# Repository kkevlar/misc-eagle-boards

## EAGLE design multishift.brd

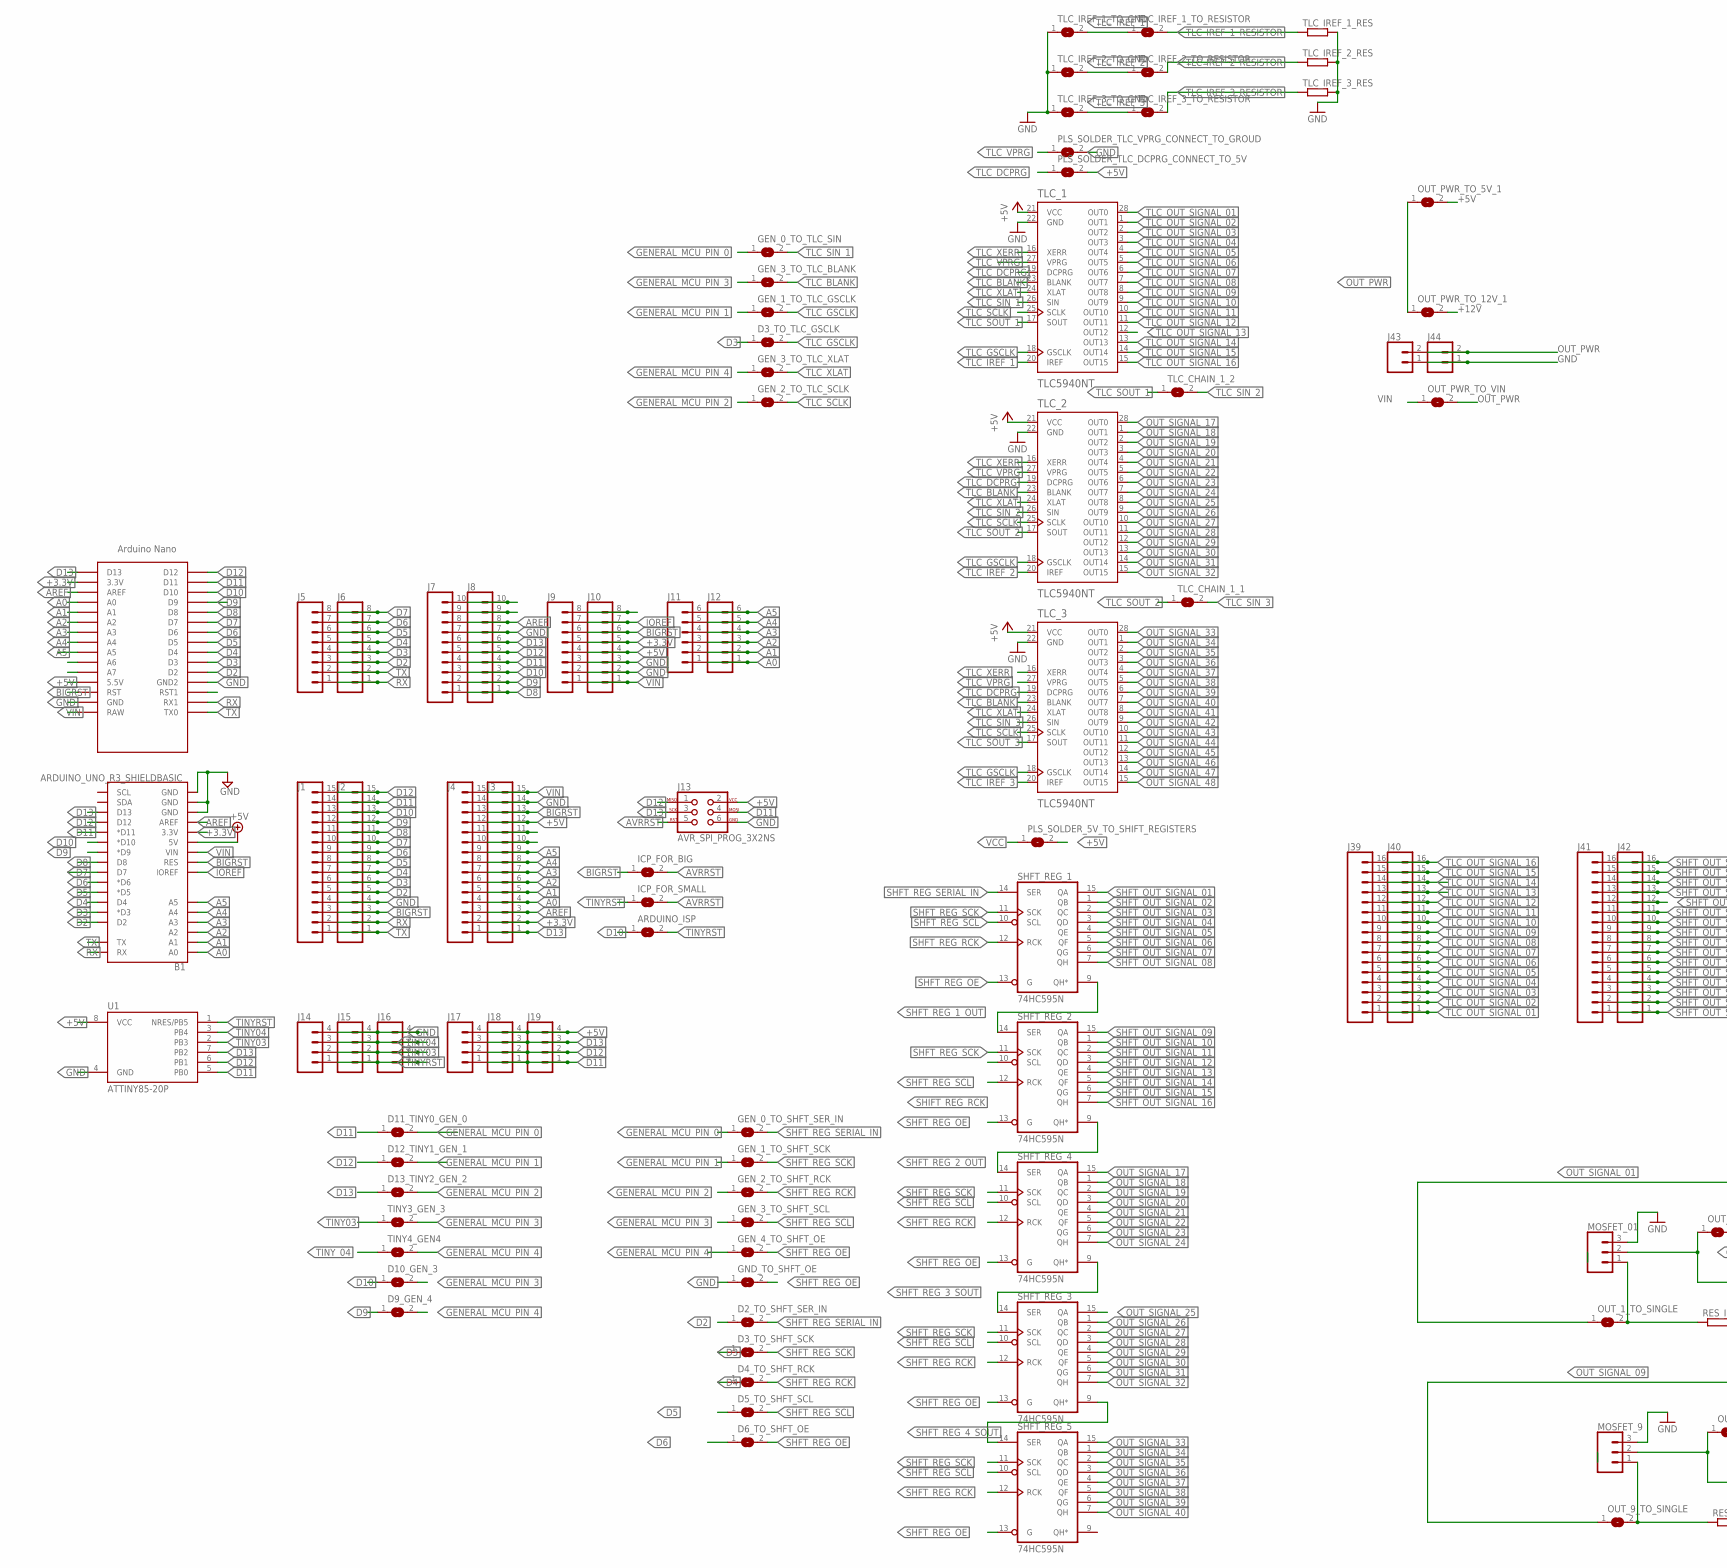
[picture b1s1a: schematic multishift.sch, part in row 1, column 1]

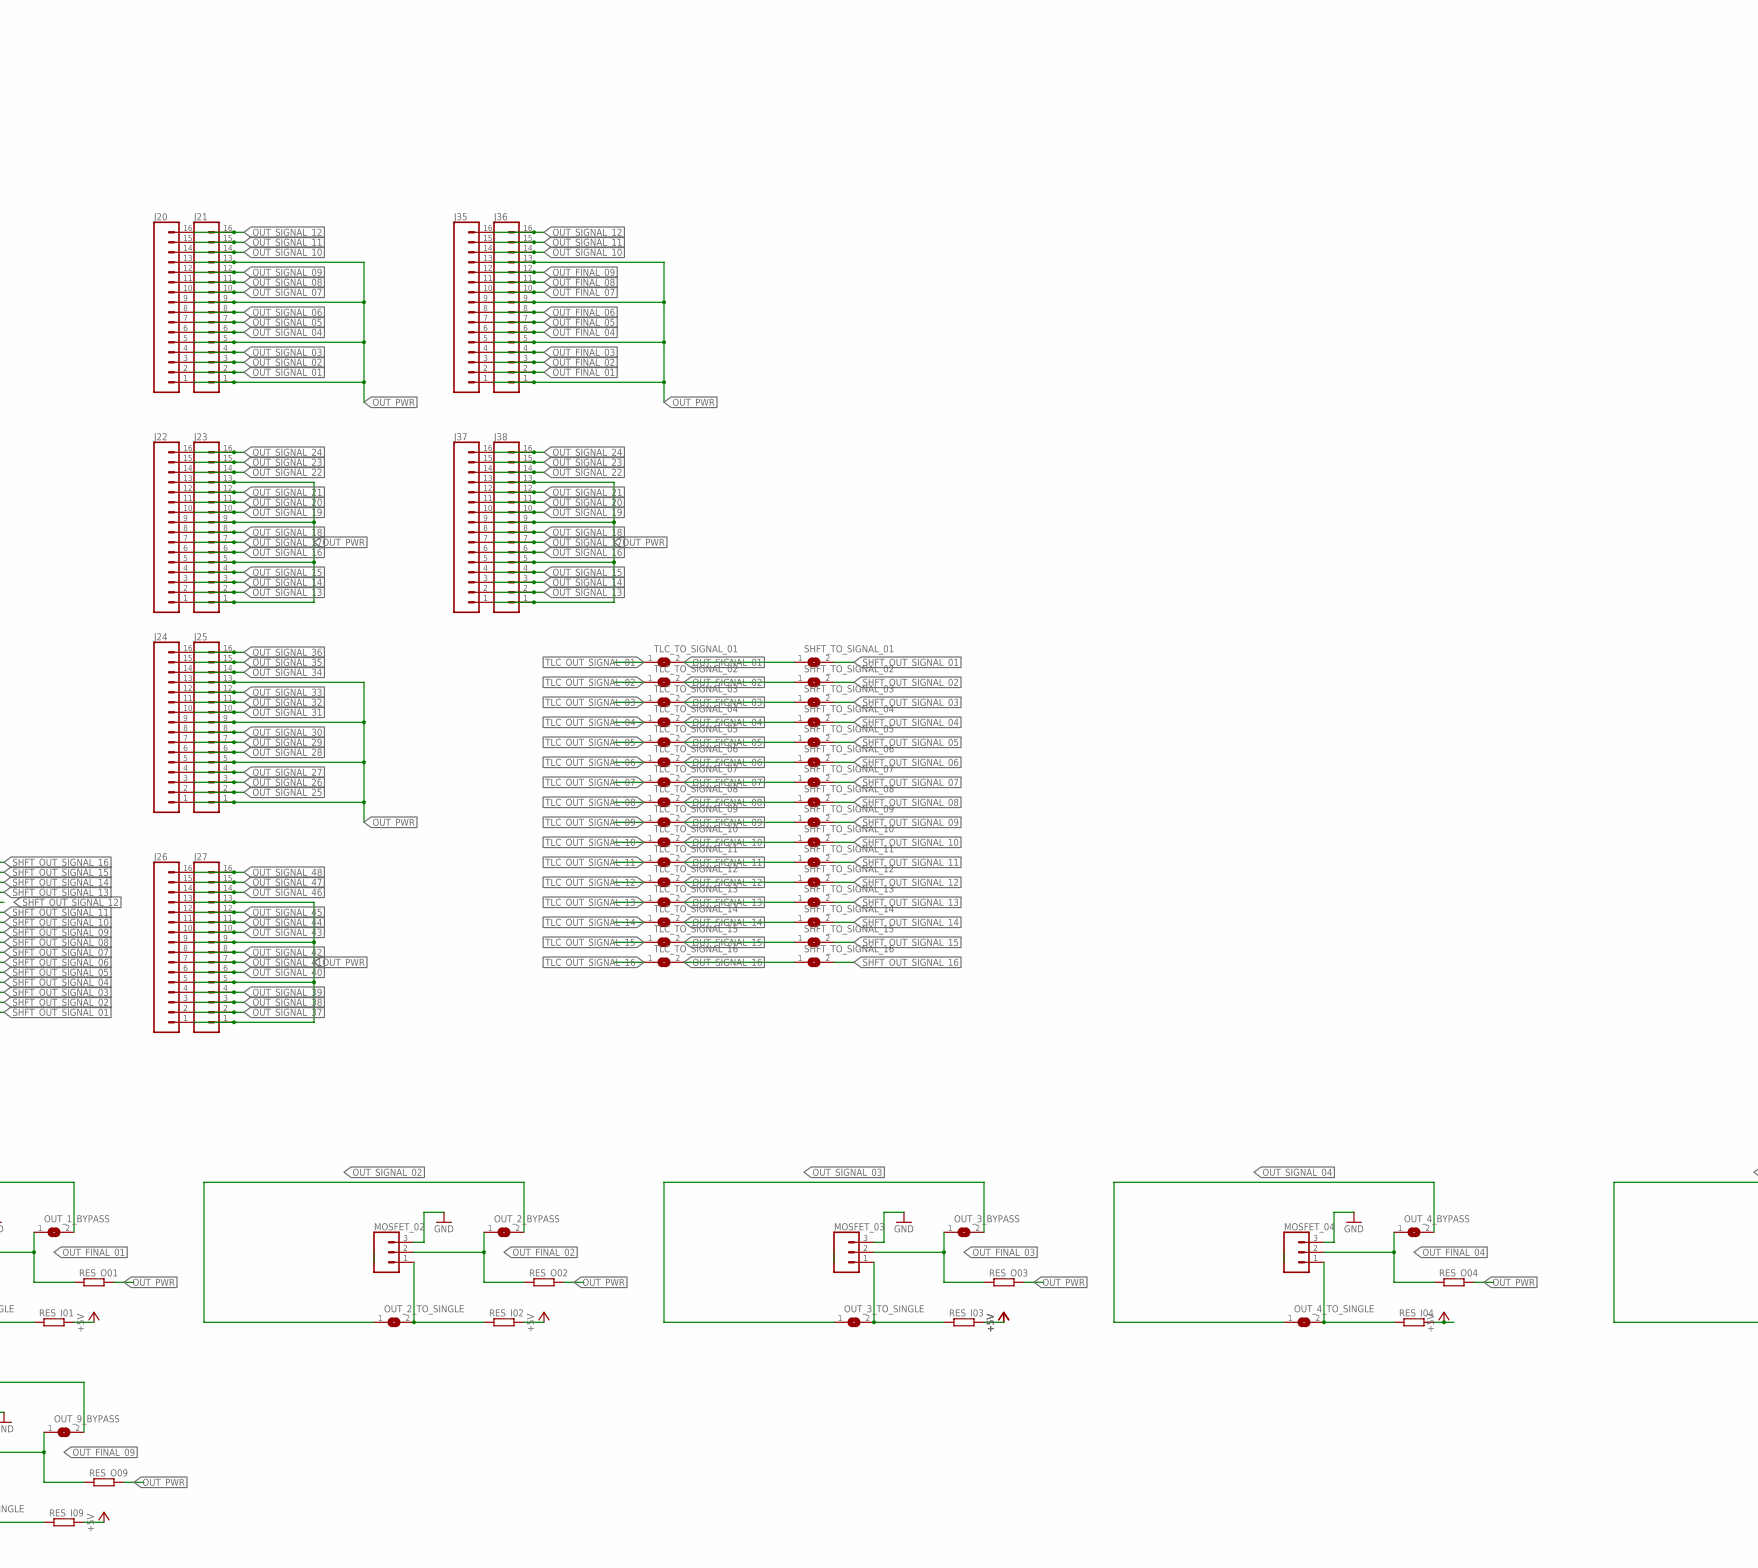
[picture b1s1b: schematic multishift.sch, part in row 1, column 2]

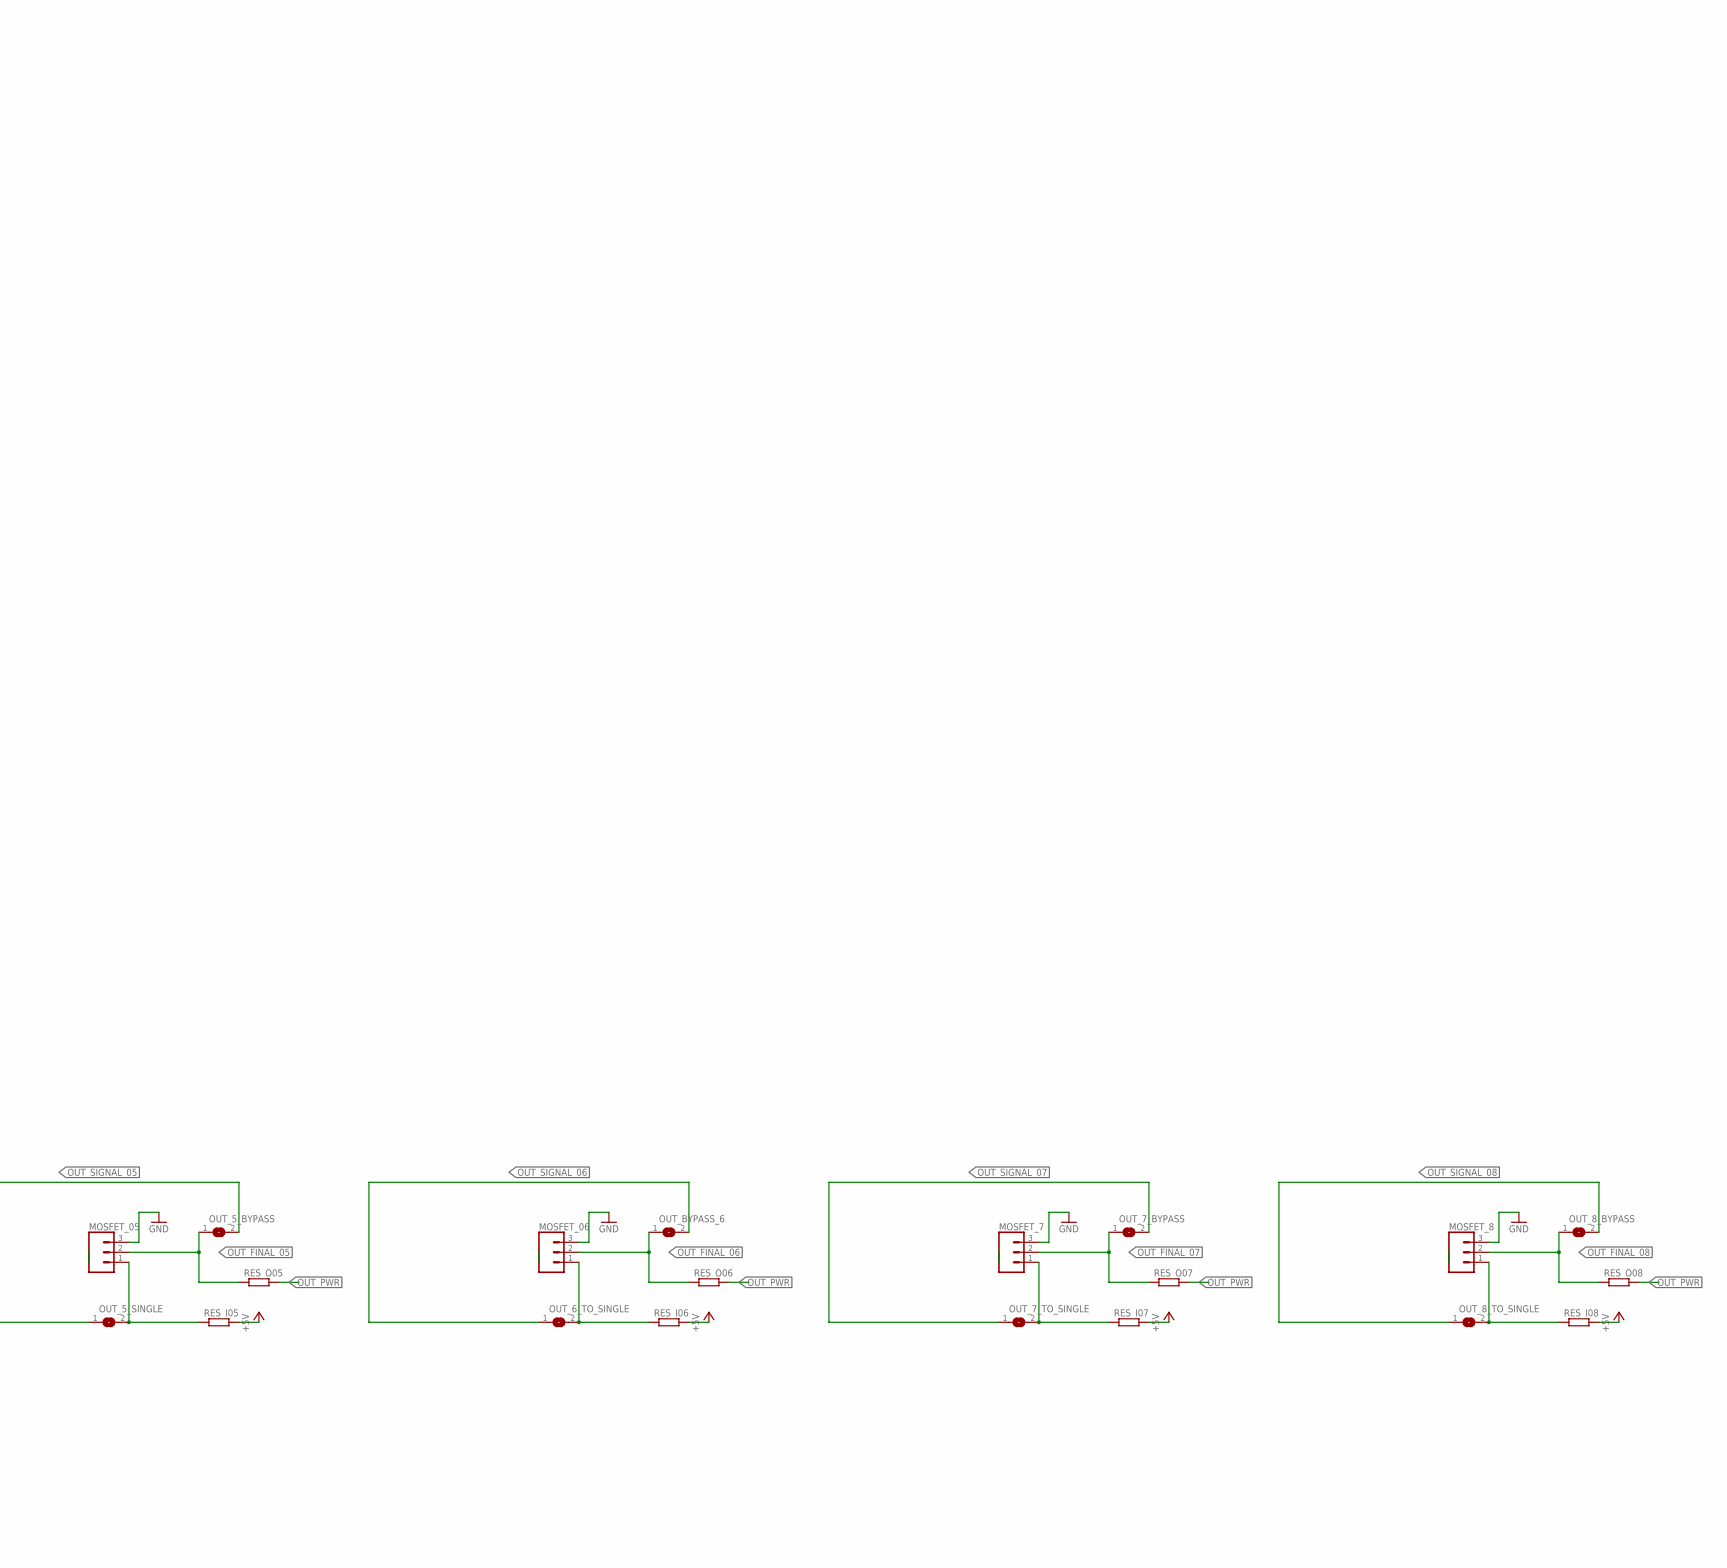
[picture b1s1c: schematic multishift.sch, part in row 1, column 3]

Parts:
ARDUINO_ISP: SJ
B1: ARDUINO_UNO_R3_SHIELDBASIC; UNO_R3_SHIELD
D2_TO_SHFT_SER_IN, D3_TO_SHFT_SCK, D3_TO_TLC_GSCLK, D4_TO_SHFT_RCK, D5_TO_SHFT_SCL, D6_TO_SHFT_OE, D9_GEN_4, D10_GEN_3, D11_TINY0_GEN_0, D12_TINY1_GEN_1, D13_TINY2_GEN_2: SJ
GEN_0_TO_SHFT_SER_IN, GEN_0_TO_TLC_SIN, GEN_1_TO_SHFT_SCK, GEN_1_TO_TLC_GSCLK, GEN_2_TO_SHFT_RCK, GEN_2_TO_TLC_SCLK, GEN_3_TO_SHFT_SCL, GEN_3_TO_TLC_BLANK, GEN_3_TO_TLC_XLAT, GEN_4_TO_SHFT_OE: SJ
GND_TO_SHFT_OE: SJ
ICP_FOR_BIG: SJ
ICP_FOR_SMALL: SJ
J1, J2, J3, J4: CONN_15; 1X15
J5, J6, J9, J10: CONN_08"; 1X08
J7, J8: CONN_10"; 1X10
J11, J12: CONN_06SILK_FEMALE_PTH; 1X06
J13: AVR_SPI_PROG_3X2NS; 2X3-NS
J14, J15, J16, J17, J18, J19: CONN_04; 1X04
J20, J21, J22, J23, J24, J25, J26, J27, J35, J36, J37, J38, J39, J40, J41, J42: CONN_16; 1X16
J43, J44: CONN_025MM; SCREWTERMINAL-5MM-2
MOSFET_01, MOSFET_02, MOSFET_03, MOSFET_04, MOSFET_05, MOSFET_06, MOSFET_7, MOSFET_8, MOSFET_9: CONN_03; 1X03
OUT_1_BYPASS, OUT_1_TO_SINGLE, OUT_2_BYPASS, OUT_2_TO_SINGLE, OUT_3_BYPASS, OUT_3_TO_SINGLE, OUT_4_BYPASS, OUT_4_TO_SINGLE, OUT_5_BYPASS, OUT_5_SINGLE, OUT_6_TO_SINGLE, OUT_7_BYPASS, OUT_7_TO_SINGLE, OUT_8_BYPASS, OUT_8_TO_SINGLE, OUT_9_BYPASS, OUT_9_TO_SINGLE: SJ
OUT_BYPASS_6: SJ
OUT_PWR_TO_5V_1, OUT_PWR_TO_12V_1: SJ
OUT_PWR_TO_VIN: SJ
PLS_SOLDER_5V_TO_SHIFT_REGISTERS: SJ
PLS_SOLDER_TLC_DCPRG_CONNECT_TO_5V: SJ
PLS_SOLDER_TLC_VPRG_CONNECT_TO_GROUD: SJ
RES_I01, RES_I02, RES_I03, RES_I04, RES_I05, RES_I06, RES_I07, RES_I08, RES_I09: R-EU_0204/7; 0204/7
RES_O01, RES_O02, RES_O03, RES_O04, RES_O05, RES_O06, RES_O07, RES_O08, RES_O09: R-EU_0204/7; 0204/7
SHFT_REG_1, SHFT_REG_2, SHFT_REG_3, SHFT_REG_4, SHFT_REG_5: 74HC595N; DIL16
SHFT_TO_SIGNAL_01, SHFT_TO_SIGNAL_02, SHFT_TO_SIGNAL_03, SHFT_TO_SIGNAL_04, SHFT_TO_SIGNAL_05, SHFT_TO_SIGNAL_06, SHFT_TO_SIGNAL_07, SHFT_TO_SIGNAL_08, SHFT_TO_SIGNAL_09, SHFT_TO_SIGNAL_10, SHFT_TO_SIGNAL_11, SHFT_TO_SIGNAL_12, SHFT_TO_SIGNAL_13, SHFT_TO_SIGNAL_14, SHFT_TO_SIGNAL_15, SHFT_TO_SIGNAL_16: SJ
TINY3_GEN_3, TINY4_GEN4: SJ
TLC_1, TLC_2, TLC_3: TLC5940NT; DIL28-3
TLC_CHAIN_1_1, TLC_CHAIN_1_2: SJ
TLC_IREF_1_RES, TLC_IREF_2_RES, TLC_IREF_3_RES: R-EU_0204/7; 0204/7
TLC_IREF_1_TO_GND, TLC_IREF_1_TO_RESISTOR, TLC_IREF_2_TO_GND, TLC_IREF_2_TO_RESISTOR, TLC_IREF_3_TO_GND, TLC_IREF_3_TO_RESISTOR: SJ
TLC_TO_SIGNAL_01, TLC_TO_SIGNAL_02, TLC_TO_SIGNAL_03, TLC_TO_SIGNAL_04, TLC_TO_SIGNAL_05, TLC_TO_SIGNAL_06, TLC_TO_SIGNAL_07, TLC_TO_SIGNAL_08, TLC_TO_SIGNAL_09, TLC_TO_SIGNAL_10, TLC_TO_SIGNAL_11, TLC_TO_SIGNAL_12, TLC_TO_SIGNAL_13, TLC_TO_SIGNAL_14, TLC_TO_SIGNAL_15, TLC_TO_SIGNAL_16: SJ
U1: ATTINY85-20P; PDIP08_300MIL
U$1: NANO

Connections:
+3.3V: B1.3.3V, J3.2, J4.2, J9.5, J10.5, U$1.3.3V
+5V: B1.5V, J3.12, J4.12, J9.4, J10.4, J13.2, J17.4, J18.4, J19.4, OUT_PWR_TO_5V_1.2, PLS_SOLDER_5V_TO_SHIFT_REGISTERS.2, PLS_SOLDER_TLC_DCPRG_CONNECT_TO_5V.2, RES_I01.2, RES_I02.2, RES_I03.2, RES_I04.2, RES_I05.2, RES_I06.2, RES_I07.2, RES_I08.2, RES_I09.2, TLC_1.21 (VCC), TLC_2.21 (VCC), TLC_3.21 (VCC), U1.8 (VCC), U$1.5V (5.5V)
+12V: OUT_PWR_TO_12V_1.2
A0: B1.A0, J3.4, J4.4, J11.1, J12.1, U$1.A0
A1: B1.A1, J3.5, J4.5, J11.2, J12.2, U$1.A1
A2: B1.A2, J3.6, J4.6, J11.3, J12.3, U$1.A2
A3: B1.A3, J3.7, J4.7, J11.4, J12.4, U$1.A3
A4: B1.A4, J3.8, J4.8, J11.5, J12.5, U$1.A4
A5: B1.A5, J3.9, J4.9, J11.6, J12.6, U$1.A5
AREF: B1.AREF, J3.3, J4.3, J7.8, J8.8, U$1.AREF
AVRRST: ICP_FOR_BIG.2, ICP_FOR_SMALL.2, J13.5
BIGRST: B1.RES, ICP_FOR_BIG.1, J1.3, J2.3, J3.13, J4.13, J9.6, J10.6, U$1.RST
D2: B1.D2, D2_TO_SHFT_SER_IN.1, J1.5, J2.5, J5.3, J6.3, U$1.D2
D3: B1.D3 (*D3), D3_TO_SHFT_SCK.1, D3_TO_TLC_GSCLK.1, J1.6, J2.6, J5.4, J6.4, U$1.D3
D4: B1.D4, D4_TO_SHFT_RCK.1, J1.7, J2.7, J5.5, J6.5, U$1.D4
D5: B1.D5 (*D5), D5_TO_SHFT_SCL.1, J1.8, J2.8, J5.6, J6.6, U$1.D5
D6: B1.D6 (*D6), D6_TO_SHFT_OE.1, J1.9, J2.9, J5.7, J6.7, U$1.D6
D7: B1.D7, J1.10, J2.10, J5.8, J6.8, U$1.D7
D8: B1.D8, J1.11, J2.11, J7.1, J8.1, U$1.D8
D9: B1.D9 (*D9), D9_GEN_4.1, J1.12, J2.12, J7.2, J8.2, U$1.D9
D10: ARDUINO_ISP.1, B1.D10 (*D10), D10_GEN_3.1, J1.13, J2.13, J7.3, J8.3, U$1.D10
D11: B1.D11 (*D11), D11_TINY0_GEN_0.1, J1.14, J2.14, J7.4, J8.4, J13.4, J17.1, J18.1, J19.1, U1.5 (PB0), U$1.D11
D12: B1.D12, D12_TINY1_GEN_1.1, J1.15, J2.15, J7.5, J8.5, J13.1, J17.2, J18.2, J19.2, U1.6 (PB1), U$1.D12
D13: B1.D13, D13_TINY2_GEN_2.1, J3.1, J4.1, J7.6, J8.6, J13.3, J17.3, J18.3, J19.3, U1.7 (PB2), U$1.D13
GENERAL_MCU_PIN_0: D11_TINY0_GEN_0.2, GEN_0_TO_SHFT_SER_IN.1, GEN_0_TO_TLC_SIN.1
GENERAL_MCU_PIN_1: D12_TINY1_GEN_1.2, GEN_1_TO_SHFT_SCK.1, GEN_1_TO_TLC_GSCLK.1
GENERAL_MCU_PIN_2: D13_TINY2_GEN_2.2, GEN_2_TO_SHFT_RCK.1, GEN_2_TO_TLC_SCLK.1
GENERAL_MCU_PIN_3: D10_GEN_3.2, GEN_3_TO_SHFT_SCL.1, GEN_3_TO_TLC_BLANK.1, TINY3_GEN_3.2
GENERAL_MCU_PIN_4: D9_GEN_4.2, GEN_3_TO_TLC_XLAT.1, GEN_4_TO_SHFT_OE.1, TINY4_GEN4.2
GND: B1.GND@0 (GND), B1.GND@1 (GND), B1.GND@2 (GND), GND_TO_SHFT_OE.1, J1.4, J2.4, J3.14, J4.14, J7.7, J8.7, J9.2, J9.3, J10.2, J10.3, J13.6, J14.4, J15.4, J16.4, J43.1, J44.1, MOSFET_01.3, MOSFET_02.3, MOSFET_03.3, MOSFET_04.3, MOSFET_05.3, MOSFET_06.3, MOSFET_7.3, MOSFET_8.3, MOSFET_9.3, PLS_SOLDER_TLC_VPRG_CONNECT_TO_GROUD.2, SHFT_REG_1.8 (GND), SHFT_REG_2.8 (GND), SHFT_REG_3.8 (GND), SHFT_REG_4.8 (GND), SHFT_REG_5.8 (GND), TLC_1.22 (GND), TLC_2.22 (GND), TLC_3.22 (GND), TLC_IREF_1_RES.2, TLC_IREF_1_TO_GND.1, TLC_IREF_2_RES.2, TLC_IREF_2_TO_GND.1, TLC_IREF_3_RES.2, TLC_IREF_3_TO_GND.1, U1.4 (GND), U$1.GND, U$1.GND1 (GND2)
IOREF: B1.IOREF, J9.7, J10.7
unnamed: J9.8, J10.8
unnamed: J3.11, J4.11
unnamed: J3.10, J4.10
unnamed: J7.9, J8.9
unnamed: J7.10, J8.10
unnamed: MOSFET_01.1, OUT_1_TO_SINGLE.2, RES_I01.1
unnamed: MOSFET_9.1, OUT_9_TO_SINGLE.2, RES_I09.1
unnamed: MOSFET_02.1, OUT_2_TO_SINGLE.2, RES_I02.1
unnamed: MOSFET_03.1, OUT_3_TO_SINGLE.2, RES_I03.1
unnamed: MOSFET_04.1, OUT_4_TO_SINGLE.2, RES_I04.1
unnamed: MOSFET_05.1, OUT_5_SINGLE.2, RES_I05.1
unnamed: MOSFET_06.1, OUT_6_TO_SINGLE.2, RES_I06.1
unnamed: MOSFET_7.1, OUT_7_TO_SINGLE.2, RES_I07.1
unnamed: MOSFET_8.1, OUT_8_TO_SINGLE.2, RES_I08.1
OUT_FINAL_01: J35.2, J36.2, MOSFET_01.2, OUT_1_BYPASS.1, RES_O01.1
OUT_FINAL_02: J35.3, J36.3, MOSFET_02.2, OUT_2_BYPASS.1, RES_O02.1
OUT_FINAL_03: J35.4, J36.4, MOSFET_03.2, OUT_3_BYPASS.1, RES_O03.1
OUT_FINAL_04: J35.6, J36.6, MOSFET_04.2, OUT_4_BYPASS.1, RES_O04.1
OUT_FINAL_05: J35.7, J36.7, MOSFET_05.2, OUT_5_BYPASS.1, RES_O05.1
OUT_FINAL_06: J35.8, J36.8, MOSFET_06.2, OUT_BYPASS_6.1, RES_O06.1
OUT_FINAL_07: J35.10, J36.10, MOSFET_7.2, OUT_7_BYPASS.1, RES_O07.1
OUT_FINAL_08: J35.11, J36.11, MOSFET_8.2, OUT_8_BYPASS.1, RES_O08.1
OUT_FINAL_09: J35.12, J36.12, MOSFET_9.2, OUT_9_BYPASS.1, RES_O09.1
OUT_PWR: J20.1, J20.5, J20.9, J20.13, J21.1, J21.5, J21.9, J21.13, J22.1, J22.5, J22.9, J22.13, J23.1, J23.5, J23.9, J23.13, J24.1, J24.5, J24.9, J24.13, J25.1, J25.5, J25.9, J25.13, J26.1, J26.5, J26.9, J26.13, J27.1, J27.5, J27.9, J27.13, J35.1, J35.5, J35.9, J35.13, J36.1, J36.5, J36.9, J36.13, J37.1, J37.5, J37.9, J37.13, J38.1, J38.5, J38.9, J38.13, J43.2, J44.2, OUT_PWR_TO_5V_1.1, OUT_PWR_TO_12V_1.1, OUT_PWR_TO_VIN.2, RES_O01.2, RES_O02.2, RES_O03.2, RES_O04.2, RES_O05.2, RES_O06.2, RES_O07.2, RES_O08.2, RES_O09.2
OUT_SIGNAL_01: J20.2, J21.2, OUT_1_BYPASS.2, OUT_1_TO_SINGLE.1, SHFT_TO_SIGNAL_01.1, TLC_TO_SIGNAL_01.2
OUT_SIGNAL_02: J20.3, J21.3, OUT_2_BYPASS.2, OUT_2_TO_SINGLE.1, SHFT_TO_SIGNAL_02.1, TLC_TO_SIGNAL_02.2
OUT_SIGNAL_03: J20.4, J21.4, OUT_3_BYPASS.2, OUT_3_TO_SINGLE.1, SHFT_TO_SIGNAL_03.1, TLC_TO_SIGNAL_03.2
OUT_SIGNAL_04: J20.6, J21.6, OUT_4_BYPASS.2, OUT_4_TO_SINGLE.1, SHFT_TO_SIGNAL_04.1, TLC_TO_SIGNAL_04.2
OUT_SIGNAL_05: J20.7, J21.7, OUT_5_BYPASS.2, OUT_5_SINGLE.1, SHFT_TO_SIGNAL_05.1, TLC_TO_SIGNAL_05.2
OUT_SIGNAL_06: J20.8, J21.8, OUT_6_TO_SINGLE.1, OUT_BYPASS_6.2, SHFT_TO_SIGNAL_06.1, TLC_TO_SIGNAL_06.2
OUT_SIGNAL_07: J20.10, J21.10, OUT_7_BYPASS.2, OUT_7_TO_SINGLE.1, SHFT_TO_SIGNAL_07.1, TLC_TO_SIGNAL_07.2
OUT_SIGNAL_08: J20.11, J21.11, OUT_8_BYPASS.2, OUT_8_TO_SINGLE.1, SHFT_TO_SIGNAL_08.1, TLC_TO_SIGNAL_08.2
OUT_SIGNAL_09: J20.12, J21.12, OUT_9_BYPASS.2, OUT_9_TO_SINGLE.1, SHFT_TO_SIGNAL_09.1, TLC_TO_SIGNAL_09.2
OUT_SIGNAL_10: J20.14, J21.14, J35.14, J36.14, SHFT_TO_SIGNAL_10.1, TLC_TO_SIGNAL_10.2
OUT_SIGNAL_11: J20.15, J21.15, J35.15, J36.15, SHFT_TO_SIGNAL_11.1, TLC_TO_SIGNAL_11.2
OUT_SIGNAL_12: J20.16, J21.16, J35.16, J36.16, SHFT_TO_SIGNAL_12.1, TLC_TO_SIGNAL_12.2
OUT_SIGNAL_13: J22.2, J23.2, J37.2, J38.2, SHFT_TO_SIGNAL_13.1, TLC_TO_SIGNAL_13.2
OUT_SIGNAL_14: J22.3, J23.3, J37.3, J38.3, SHFT_TO_SIGNAL_14.1, TLC_TO_SIGNAL_14.2
OUT_SIGNAL_15: J22.4, J23.4, J37.4, J38.4, SHFT_TO_SIGNAL_15.1, TLC_TO_SIGNAL_15.2
OUT_SIGNAL_16: J22.6, J23.6, J37.6, J38.6, SHFT_TO_SIGNAL_16.1, TLC_TO_SIGNAL_16.2
OUT_SIGNAL_17: J22.7, J23.7, J37.7, J38.7, SHFT_REG_4.15 (QA), TLC_2.28 (OUT0)
OUT_SIGNAL_18: J22.8, J23.8, J37.8, J38.8, SHFT_REG_4.1 (QB), TLC_2.1 (OUT1)
OUT_SIGNAL_19: J22.10, J23.10, J37.10, J38.10, SHFT_REG_4.2 (QC), TLC_2.2 (OUT2)
OUT_SIGNAL_20: J22.11, J23.11, J37.11, J38.11, SHFT_REG_4.3 (QD), TLC_2.3 (OUT3)
OUT_SIGNAL_21: J22.12, J23.12, J37.12, J38.12, SHFT_REG_4.4 (QE), TLC_2.4 (OUT4)
OUT_SIGNAL_22: J22.14, J23.14, J37.14, J38.14, SHFT_REG_4.5 (QF), TLC_2.5 (OUT5)
OUT_SIGNAL_23: J22.15, J23.15, J37.15, J38.15, SHFT_REG_4.6 (QG), TLC_2.6 (OUT6)
OUT_SIGNAL_24: J22.16, J23.16, J37.16, J38.16, SHFT_REG_4.7 (QH), TLC_2.7 (OUT7)
OUT_SIGNAL_25: J24.2, J25.2, SHFT_REG_3.15 (QA), TLC_2.8 (OUT8)
OUT_SIGNAL_26: J24.3, J25.3, SHFT_REG_3.1 (QB), TLC_2.9 (OUT9)
OUT_SIGNAL_27: J24.4, J25.4, SHFT_REG_3.2 (QC), TLC_2.10 (OUT10)
OUT_SIGNAL_28: J24.6, J25.6, SHFT_REG_3.3 (QD), TLC_2.11 (OUT11)
OUT_SIGNAL_29: J24.7, J25.7, SHFT_REG_3.4 (QE), TLC_2.12 (OUT12)
OUT_SIGNAL_30: J24.8, J25.8, SHFT_REG_3.5 (QF), TLC_2.13 (OUT13)
OUT_SIGNAL_31: J24.10, J25.10, SHFT_REG_3.6 (QG), TLC_2.14 (OUT14)
OUT_SIGNAL_32: J24.11, J25.11, SHFT_REG_3.7 (QH), TLC_2.15 (OUT15)
OUT_SIGNAL_33: J24.12, J25.12, SHFT_REG_5.15 (QA), TLC_3.28 (OUT0)
OUT_SIGNAL_34: J24.14, J25.14, SHFT_REG_5.1 (QB), TLC_3.1 (OUT1)
OUT_SIGNAL_35: J24.15, J25.15, SHFT_REG_5.2 (QC), TLC_3.2 (OUT2)
OUT_SIGNAL_36: J24.16, J25.16, SHFT_REG_5.3 (QD), TLC_3.3 (OUT3)
OUT_SIGNAL_37: J26.2, J27.2, SHFT_REG_5.4 (QE), TLC_3.4 (OUT4)
OUT_SIGNAL_38: J26.3, J27.3, SHFT_REG_5.5 (QF), TLC_3.5 (OUT5)
OUT_SIGNAL_39: J26.4, J27.4, SHFT_REG_5.6 (QG), TLC_3.6 (OUT6)
OUT_SIGNAL_40: J26.6, J27.6, SHFT_REG_5.7 (QH), TLC_3.7 (OUT7)
OUT_SIGNAL_41: J26.7, J27.7, TLC_3.8 (OUT8)
OUT_SIGNAL_42: J26.8, J27.8, TLC_3.9 (OUT9)
OUT_SIGNAL_43: J26.10, J27.10, TLC_3.10 (OUT10)
OUT_SIGNAL_44: J26.11, J27.11, TLC_3.11 (OUT11)
OUT_SIGNAL_45: J26.12, J27.12, TLC_3.12 (OUT12)
OUT_SIGNAL_46: J26.14, J27.14, TLC_3.13 (OUT13)
OUT_SIGNAL_47: J26.15, J27.15, TLC_3.14 (OUT14)
OUT_SIGNAL_48: J26.16, J27.16, TLC_3.15 (OUT15)
RX: B1.RX, J1.2, J2.2, J5.1, J6.1, U$1.RX1
SHFT_OUT_SIGNAL_01: J41.1, J42.1, SHFT_REG_1.15 (QA), SHFT_TO_SIGNAL_01.2
SHFT_OUT_SIGNAL_02: J41.2, J42.2, SHFT_REG_1.1 (QB), SHFT_TO_SIGNAL_02.2
SHFT_OUT_SIGNAL_03: J41.3, J42.3, SHFT_REG_1.2 (QC), SHFT_TO_SIGNAL_03.2
SHFT_OUT_SIGNAL_04: J41.4, J42.4, SHFT_REG_1.3 (QD), SHFT_TO_SIGNAL_04.2
SHFT_OUT_SIGNAL_05: J41.5, J42.5, SHFT_REG_1.4 (QE), SHFT_TO_SIGNAL_05.2
SHFT_OUT_SIGNAL_06: J41.6, J42.6, SHFT_REG_1.5 (QF), SHFT_TO_SIGNAL_06.2
SHFT_OUT_SIGNAL_07: J41.7, J42.7, SHFT_REG_1.6 (QG), SHFT_TO_SIGNAL_07.2
SHFT_OUT_SIGNAL_08: J41.8, J42.8, SHFT_REG_1.7 (QH), SHFT_TO_SIGNAL_08.2
SHFT_OUT_SIGNAL_09: J41.9, J42.9, SHFT_REG_2.15 (QA), SHFT_TO_SIGNAL_09.2
SHFT_OUT_SIGNAL_10: J41.10, J42.10, SHFT_REG_2.1 (QB), SHFT_TO_SIGNAL_10.2
SHFT_OUT_SIGNAL_11: J41.11, J42.11, SHFT_REG_2.2 (QC), SHFT_TO_SIGNAL_11.2
SHFT_OUT_SIGNAL_12: J41.12, J42.12, SHFT_REG_2.3 (QD), SHFT_TO_SIGNAL_12.2
SHFT_OUT_SIGNAL_13: J41.13, J42.13, SHFT_REG_2.4 (QE), SHFT_TO_SIGNAL_13.2
SHFT_OUT_SIGNAL_14: J41.14, J42.14, SHFT_REG_2.5 (QF), SHFT_TO_SIGNAL_14.2
SHFT_OUT_SIGNAL_15: J41.15, J42.15, SHFT_REG_2.6 (QG), SHFT_TO_SIGNAL_15.2
SHFT_OUT_SIGNAL_16: J41.16, J42.16, SHFT_REG_2.7 (QH), SHFT_TO_SIGNAL_16.2
SHFT_REG_1_OUT: SHFT_REG_1.9 (QH*), SHFT_REG_2.14 (SER)
SHFT_REG_2_OUT: SHFT_REG_2.9 (QH*), SHFT_REG_4.14 (SER)
SHFT_REG_3_SOUT: SHFT_REG_3.14 (SER), SHFT_REG_4.9 (QH*)
SHFT_REG_4_SOUT: SHFT_REG_3.9 (QH*), SHFT_REG_5.14 (SER)
SHFT_REG_OE: D6_TO_SHFT_OE.2, GEN_4_TO_SHFT_OE.2, GND_TO_SHFT_OE.2, SHFT_REG_1.13 (G), SHFT_REG_2.13 (G), SHFT_REG_3.13 (G), SHFT_REG_4.13 (G), SHFT_REG_5.13 (G)
SHFT_REG_RCK: D4_TO_SHFT_RCK.2, GEN_2_TO_SHFT_RCK.2, SHFT_REG_1.12 (RCK), SHFT_REG_3.12 (RCK), SHFT_REG_4.12 (RCK), SHFT_REG_5.12 (RCK)
SHFT_REG_SCK: D3_TO_SHFT_SCK.2, GEN_1_TO_SHFT_SCK.2, SHFT_REG_1.11 (SCK), SHFT_REG_2.11 (SCK), SHFT_REG_3.11 (SCK), SHFT_REG_4.11 (SCK), SHFT_REG_5.11 (SCK)
SHFT_REG_SCL: D5_TO_SHFT_SCL.2, GEN_3_TO_SHFT_SCL.2, SHFT_REG_1.10 (SCL), SHFT_REG_2.10 (SCL), SHFT_REG_3.10 (SCL), SHFT_REG_4.10 (SCL), SHFT_REG_5.10 (SCL)
SHFT_REG_SERIAL_IN: D2_TO_SHFT_SER_IN.2, GEN_0_TO_SHFT_SER_IN.2, SHFT_REG_1.14 (SER)
SHIFT_REG_RCK: SHFT_REG_2.12 (RCK)
TINY03: J14.2, J15.2, J16.2, TINY3_GEN_3.1, U1.2 (PB3)
TINY04: J14.3, J15.3, J16.3, U1.3 (PB4)
TINYRST: ARDUINO_ISP.2, ICP_FOR_SMALL.1, J14.1, J15.1, J16.1, U1.1 (NRES/PB5)
TINY_04: TINY4_GEN4.1
TLC_BLANK: GEN_3_TO_TLC_BLANK.2, TLC_1.23 (BLANK), TLC_2.23 (BLANK), TLC_3.23 (BLANK)
TLC_DCPRG: PLS_SOLDER_TLC_DCPRG_CONNECT_TO_5V.1, TLC_1.19 (DCPRG), TLC_2.19 (DCPRG), TLC_3.19 (DCPRG)
TLC_GSCLK: D3_TO_TLC_GSCLK.2, GEN_1_TO_TLC_GSCLK.2, TLC_1.18 (GSCLK), TLC_2.18 (GSCLK), TLC_3.18 (GSCLK)
TLC_IREF_1: TLC_1.20 (IREF), TLC_IREF_1_TO_GND.2, TLC_IREF_1_TO_RESISTOR.1
TLC_IREF_1_RESISTOR: TLC_IREF_1_RES.1, TLC_IREF_1_TO_RESISTOR.2
TLC_IREF_2: TLC_2.20 (IREF), TLC_IREF_2_TO_GND.2, TLC_IREF_2_TO_RESISTOR.1
TLC_IREF_2_RESISTOR: TLC_IREF_2_RES.1, TLC_IREF_2_TO_RESISTOR.2
TLC_IREF_3: TLC_3.20 (IREF), TLC_IREF_3_TO_GND.2, TLC_IREF_3_TO_RESISTOR.1
TLC_IREF_3_RESISTOR: TLC_IREF_3_RES.1, TLC_IREF_3_TO_RESISTOR.2
TLC_OUT_SIGNAL_01: J39.1, J40.1, TLC_1.28 (OUT0), TLC_TO_SIGNAL_01.1
TLC_OUT_SIGNAL_02: J39.2, J40.2, TLC_1.1 (OUT1), TLC_TO_SIGNAL_02.1
TLC_OUT_SIGNAL_03: J39.3, J40.3, TLC_1.2 (OUT2), TLC_TO_SIGNAL_03.1
TLC_OUT_SIGNAL_04: J39.4, J40.4, TLC_1.3 (OUT3), TLC_TO_SIGNAL_04.1
TLC_OUT_SIGNAL_05: J39.5, J40.5, TLC_1.4 (OUT4), TLC_TO_SIGNAL_05.1
TLC_OUT_SIGNAL_06: J39.6, J40.6, TLC_1.5 (OUT5), TLC_TO_SIGNAL_06.1
TLC_OUT_SIGNAL_07: J39.7, J40.7, TLC_1.6 (OUT6), TLC_TO_SIGNAL_07.1
TLC_OUT_SIGNAL_08: J39.8, J40.8, TLC_1.7 (OUT7), TLC_TO_SIGNAL_08.1
TLC_OUT_SIGNAL_09: J39.9, J40.9, TLC_1.8 (OUT8), TLC_TO_SIGNAL_09.1
TLC_OUT_SIGNAL_10: J39.10, J40.10, TLC_1.9 (OUT9), TLC_TO_SIGNAL_10.1
TLC_OUT_SIGNAL_11: J39.11, J40.11, TLC_1.10 (OUT10), TLC_TO_SIGNAL_11.1
TLC_OUT_SIGNAL_12: J39.12, J40.12, TLC_1.11 (OUT11), TLC_TO_SIGNAL_12.1
TLC_OUT_SIGNAL_13: J39.13, J40.13, TLC_1.12 (OUT12), TLC_TO_SIGNAL_13.1
TLC_OUT_SIGNAL_14: J39.14, J40.14, TLC_1.13 (OUT13), TLC_TO_SIGNAL_14.1
TLC_OUT_SIGNAL_15: J39.15, J40.15, TLC_1.14 (OUT14), TLC_TO_SIGNAL_15.1
TLC_OUT_SIGNAL_16: J39.16, J40.16, TLC_1.15 (OUT15), TLC_TO_SIGNAL_16.1
TLC_SCLK: GEN_2_TO_TLC_SCLK.2, TLC_1.25 (SCLK), TLC_2.25 (SCLK), TLC_3.25 (SCLK)
TLC_SIN_1: GEN_0_TO_TLC_SIN.2, TLC_1.26 (SIN)
TLC_SIN_2: TLC_2.26 (SIN), TLC_CHAIN_1_2.2
TLC_SIN_3: TLC_3.26 (SIN), TLC_CHAIN_1_1.2
TLC_SOUT_1: TLC_1.17 (SOUT), TLC_CHAIN_1_2.1
TLC_SOUT_2: TLC_2.17 (SOUT), TLC_CHAIN_1_1.1
TLC_SOUT_3: TLC_3.17 (SOUT)
TLC_VPRG: PLS_SOLDER_TLC_VPRG_CONNECT_TO_GROUD.1, TLC_1.27 (VPRG), TLC_2.27 (VPRG), TLC_3.27 (VPRG)
TLC_XERR: TLC_1.16 (XERR), TLC_2.16 (XERR), TLC_3.16 (XERR)
TLC_XLAT: GEN_3_TO_TLC_XLAT.2, TLC_1.24 (XLAT), TLC_2.24 (XLAT), TLC_3.24 (XLAT)
TX: B1.TX, J1.1, J2.1, J5.2, J6.2, U$1.TX0
VCC: PLS_SOLDER_5V_TO_SHIFT_REGISTERS.1, SHFT_REG_1.16 (VCC), SHFT_REG_2.16 (VCC), SHFT_REG_3.16 (VCC), SHFT_REG_4.16 (VCC), SHFT_REG_5.16 (VCC)
VIN: B1.VIN, J3.15, J4.15, J9.1, J10.1, OUT_PWR_TO_VIN.1, U$1.RAW

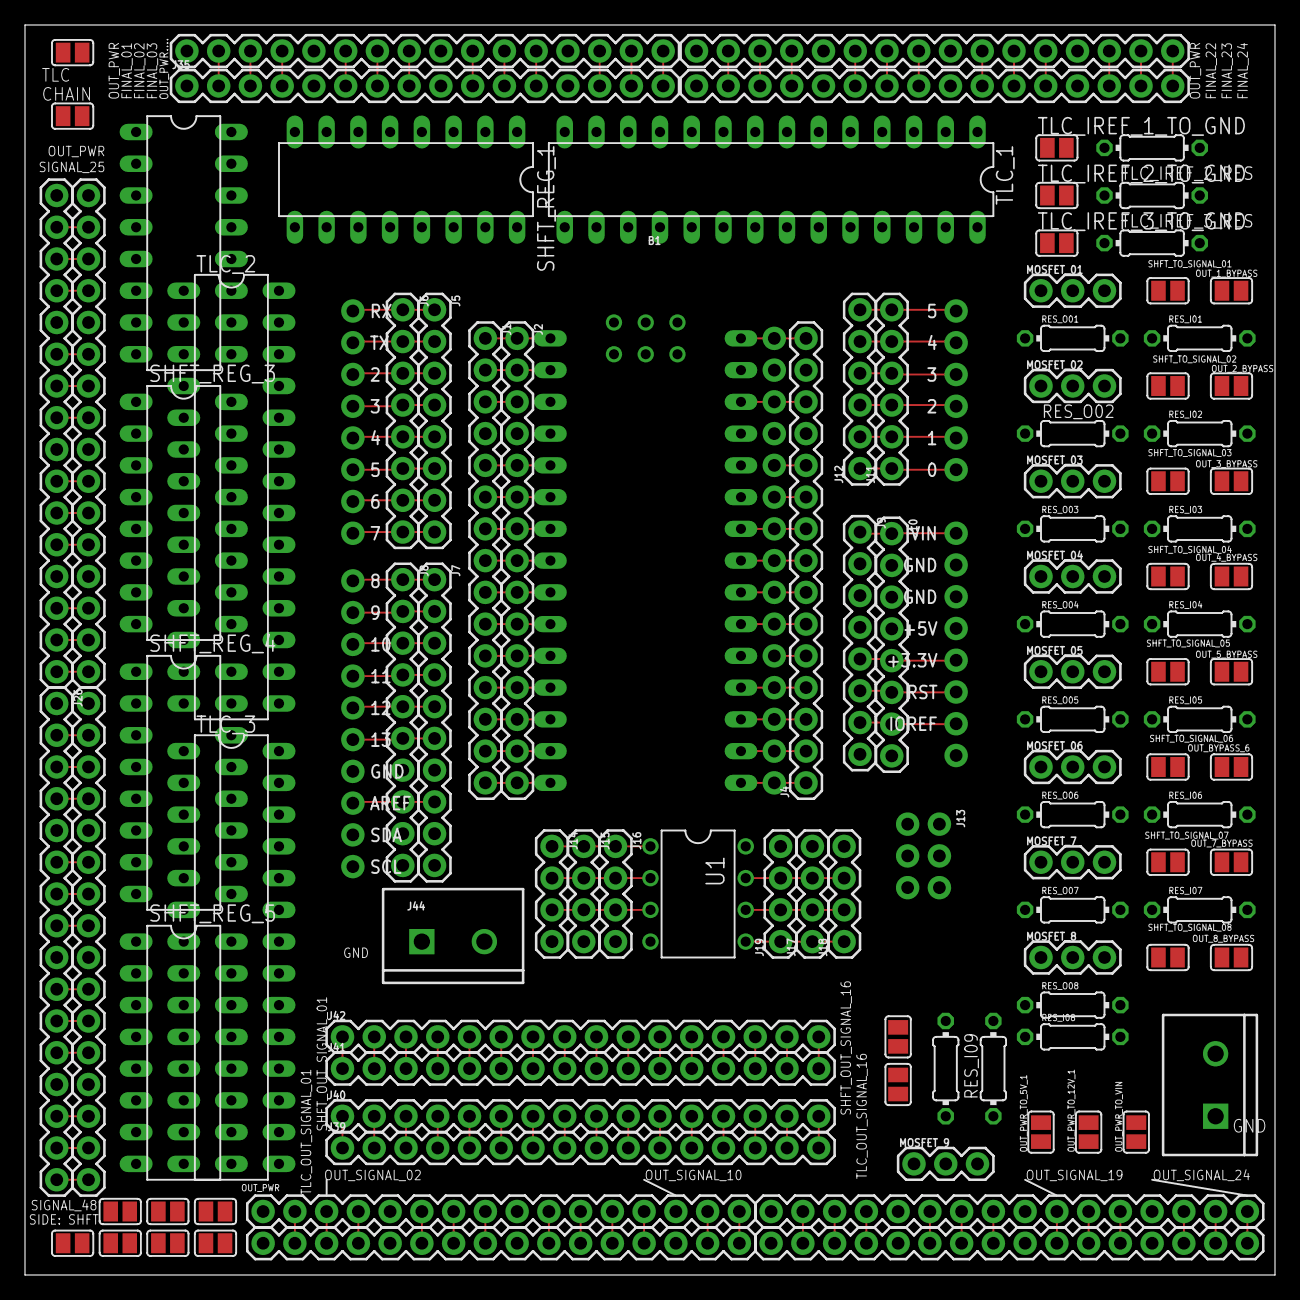
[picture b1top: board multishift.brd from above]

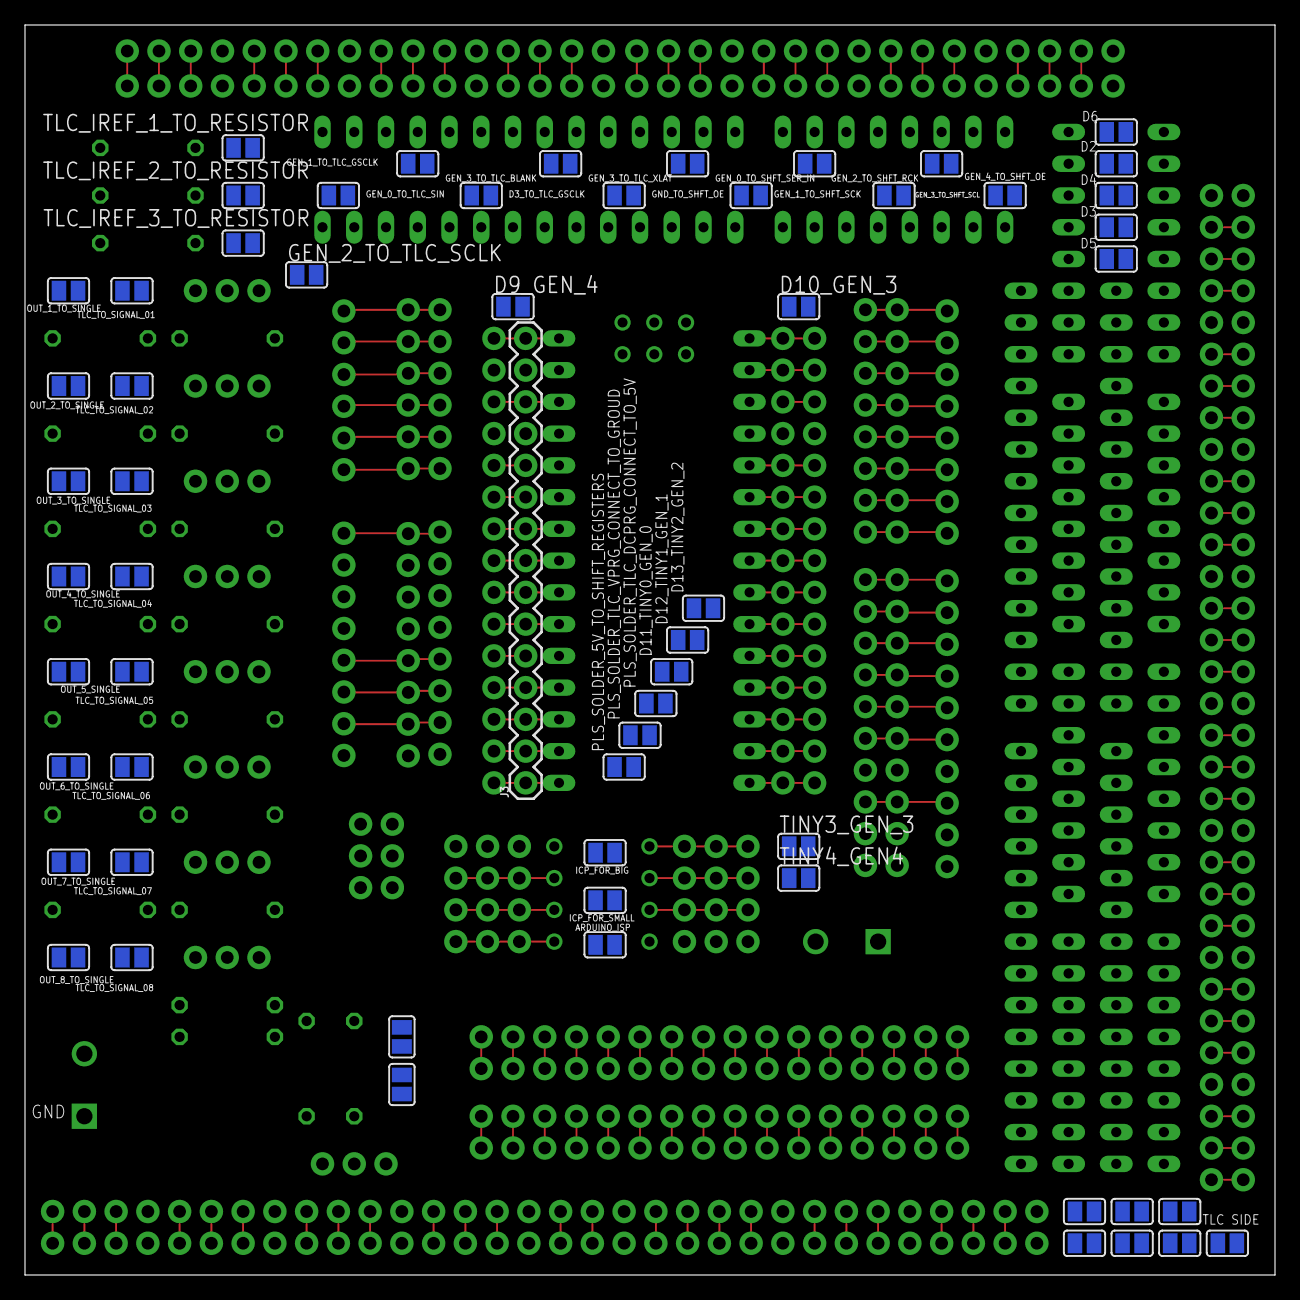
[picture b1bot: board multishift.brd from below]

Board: 2 copper layers, 100.0 x 100.0 mm, 169 parts (59 on the bottom side), 168 nets.

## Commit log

2019-05-28 unonano board
2019-06-17 lookin good
2019-10-04 multishift board
2019-10-05 added a breadboard
2019-10-11 just need to fix the outs and out finals
2019-10-15 multishift so so close
2019-10-19 so so close
2019-10-24 multishift ready for auto

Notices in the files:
parts and their libraries:
SparkFun-Boards: Licensing: Creative Commons ShareAlike 4.0 International - https://creativecommons.org/licenses/by-sa/4.0
